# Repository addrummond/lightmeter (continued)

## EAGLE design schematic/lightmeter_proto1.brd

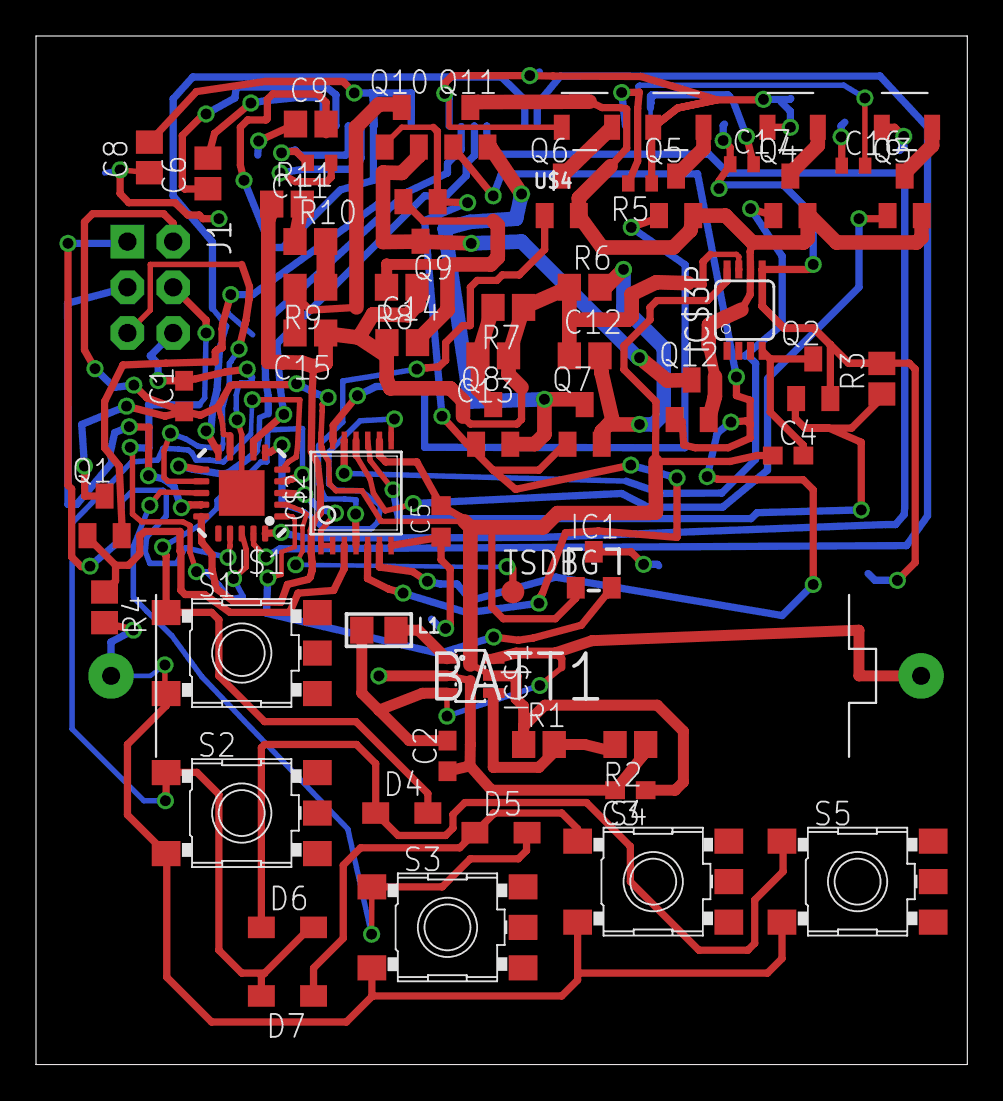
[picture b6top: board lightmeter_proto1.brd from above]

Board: 2 copper layers, 51.7 x 57.1 mm, 61 parts (0 on the bottom side), 54 nets.

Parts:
BATT1: AAA; 12BH412
C1, C4: µ1; C1608
C2, C3: 4µ7; C1608
C5: µ1; C0603K
C6, C8, C9: 1µ; C2012
C11: 1µ; C0402
C12, C13, C14, C15: 4µ7; C2012
C16: 4µ7; C0402
C17: 2µ2; C0402
D4, D5, D6, D7: SOD323-W
D8, D9, D10, D11: VEMD2523SLX01
IC1: TC1047SOT-23B; SOT-23B
IC$1: TI-TLV61220; SOT23-6L
IC$2: SN74HC164TSSOP-14; TSSOP14
IC$3P: AD8542RM; MSOP08
J1: AVR_SPI_PRG_6NS; 2X3-NS
L1: 4µ7; 0805
Q1, Q2, Q3, Q4, Q5, Q6, Q8, Q10, Q12: BSS123; SOT23
Q7, Q9, Q11: BSS84; SOT23
R1, R9, R10, R11: 1M; R2012
R2: 220k; R2012
R3, R4: 10k; R2012
R5: 390k; R0402
R6: 16k; R2012
R7: 130k; R2012
R8: 390k; R2012
S1, S2, S3, S4, S5: SKHMPSE010; SKHMPXE010
TSDBG: TPB1,27; B1,27
U$1: ATTINY1634MLF20; MLF20
U$4: UG-2864HSWEG01_0.96IN_WRAPAROUND

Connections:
AVRMISO: J1.1, U$1.17
AVRMOSI: J1.4, U$1.18
AVRRST: J1.5, U$1.12
AVRSCK: J1.3, U$1.14
DIODESW$1: IC$2.4, Q6.1
DIODESW$2: IC$2.13, Q5.1
DIODESW$3: IC$2.12, Q4.1
DIODESW$4: IC$2.11, Q3.1
GND: BATT1.-, C1.2, C2.1, C3.2, C5.1, C8.1, C9.1, C16.1, C17.1, D8.P$1, D9.P$1, D10.P$1, D11.P$1, IC1.3, IC$1.2, IC$2.7, IC$3P.5, J1.6, Q2.2, R2.1, R3.2, R4.2, R5.1, S1.3, S2.3, S3.3, S4.3, S5.3, U$1.8, U$1.GND, U$4.1, U$4.8, U$4.10, U$4.11, U$4.12, U$4.29, U$4.30
unnamed: IC$1.1, L1.2
unnamed: D8.P$2, Q6.3
unnamed: C14.2, Q9.2, R8.2
unnamed: C12.2, Q7.2, R6.2
unnamed: D9.P$2, Q5.3
unnamed: C4.2, IC$3P.4, Q2.3
unnamed: D5.C, D7.C, S4.1
unnamed: D4.C, D6.C, S5.1
unnamed: D10.P$2, Q4.3
unnamed: IC$1.4, R1.2, R2.2
unnamed: D11.P$2, Q3.3
unnamed: C16.2, U$4.27
unnamed: R9.1, R10.2
unnamed: C13.2, Q8.3, R7.2
unnamed: C6.2, U$4.2
unnamed: C6.1, U$4.3
unnamed: C8.2, C9.2, U$4.6, U$4.9
unnamed: R10.1, R11.2
unnamed: R5.2, U$4.26
unnamed: Q9.3, Q10.2, Q12.3
unnamed: C15.2, Q10.3, R9.2
unnamed: Q7.3, Q8.2, Q11.2
unnamed: TSDBG.TP, U$1.2
unnamed: C11.1, U$4.5
unnamed: C17.2, U$4.28
unnamed: IC$3P.6, Q3.2, Q4.2, Q5.2, Q6.2, Q11.3, Q12.2
unnamed: C11.2, U$4.4
unnamed: IC1.2, U$1.1
OAOUT: C12.1, C13.1, C14.1, C15.1, IC$3P.7, R6.1, R7.1, R8.1, R11.1, U$1.15
OAPWR: IC$2.10, Q2.1, R3.1
PBI$1: D4.A, S1.1, U$1.4
PBI$2: D6.A, D7.A, S2.1, U$1.5
PBI$3: D5.A, S3.1, U$1.13
SCRCLK: U$1.10, U$4.18
SCRCS: U$1.11, U$4.13
SCRDAT: U$1.19, U$4.19
SCRDC: U$1.20, U$4.15
SCRPWR: IC$2.3, Q1.1, R4.1
SCRRES: U$1.7, U$4.14
SRA: IC$2.1, IC$2.2, U$1.3
SRCLK: IC$2.8, U$1.6
STG$1: IC$2.5, Q7.1, Q8.1, Q9.1, Q10.1
STG$2: IC$2.6, Q11.1, Q12.1
VCC: BATT1.+, C2.2, IC$1.3, IC$1.6, L1.1
VREG: C1.1, C3.1, C4.1, C5.2, IC1.1, IC$1.5, IC$2.9, IC$2.14, IC$3P.8, J1.2, Q1.3, R1.1, U$1.9

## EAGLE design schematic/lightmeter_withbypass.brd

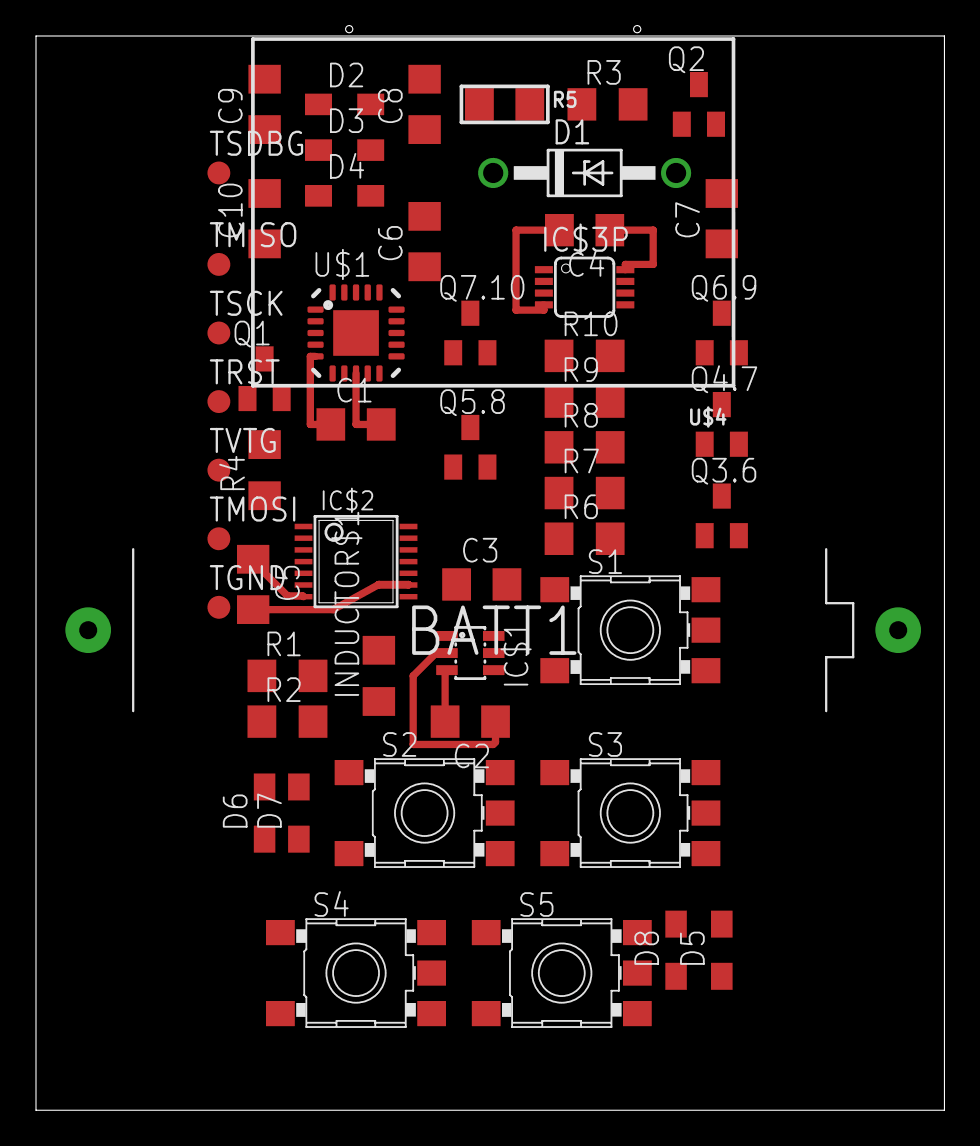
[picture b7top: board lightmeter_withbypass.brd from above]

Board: 2 copper layers, 50.5 x 59.7 mm, 54 parts (0 on the bottom side), 45 nets.

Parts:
BATT1: AAA; 12BH412
C1, C4, C5, C10: µ1; C1206
C2, C3, C6: 4µ7; C1206
C7: 2µ2; C1206
C8, C9: 2µ; C1206
D1: 1N4728; DO41Z10
D2, D3, D4, D5, D6, D7, D8: SOD323-W
IC$1: TI-TLV61220; SOT23-6L
IC$2: SN74HC164TSSOP-14; TSSOP14
IC$3P: AD8542RM; MSOP08
INDUCTOR$1: 4.7µH; R1206
Q1, Q2, Q3.6, Q4.7, Q5.8, Q6.9, Q7.10: BSS123; SOT23
R1, R9: 1M; R1206
R2: 220k; R1206
R3, R4: 10k; R1206
R5: 530k; 1206
R6: 1k; R1206
R7: 22k; R1206
R8: 330k; R1206
R10: 3.3M; R1206
S1, S2, S3, S4, S5: SKHMPSE010; SKHMPXE010
TGND: TPB1,27; B1,27
TMISO: TPB1,27; B1,27
TMOSI: TPB1,27; B1,27
TRST: TPB1,27; B1,27
TSCK: TPB1,27; B1,27
TSDBG: TPB1,27; B1,27
TVTG: TPB1,27; B1,27
U$1: ATTINY1634MLF20; MLF20
U$4: UG-2864HSWEG01_0.96IN_WRAPAROUND

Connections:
AVRMISO: TMISO.TP, U$1.17
AVRMOSI: TMOSI.TP, U$1.18
AVRRST: TRST.TP, U$1.12
AVRSCK: TSCK.TP, U$1.14
CPCLK1: C8.2, U$1.1
CPCLK2: C9.2, U$1.16
CPOUT: C10.1, D4.C, U$4.28
GND: BATT1.-, C1.2, C2.1, C3.2, C5.1, C7.2, C10.2, D1.A, IC$1.2, IC$2.7, IC$3P.5, Q1.2, Q2.2, R2.1, R3.2, R4.1, R5.2, S1.3, S2.3, S3.3, S4.3, S5.3, TGND.TP, U$1.8, U$1.GND
unnamed: IC$1.1, INDUCTOR$1.2
unnamed: C6.2, D1.C, IC$3P.6, Q3.6.3, Q4.7.3, Q5.8.3, Q6.9.3, Q7.10.3
unnamed: Q5.8.2, R8.2
unnamed: Q6.9.2, R9.2
unnamed: Q3.6.2, R6.2
unnamed: C4.2, IC$3P.4, Q2.3
unnamed: D6.C, D7.C, S4.1
unnamed: D5.C, D8.C, S5.1
unnamed: Q7.10.2, R10.2
unnamed: IC$1.4, R1.2, R2.2
unnamed: C8.1, D2.C, D3.A
unnamed: C9.1, D3.C, D4.A
unnamed: R5.1, U$4.26
unnamed: TSDBG.TP, U$1.2
unnamed: C7.1, U$4.27
OAOUT: C6.1, IC$3P.7, R6.1, R7.1, R8.1, R9.1, R10.1, U$1.15
OAPWR: IC$2.10, Q2.1, R3.1
PBI$1: D5.A, S1.1, U$1.4
PBI$2: D7.A, D8.A, S2.1, U$1.5
PBI$3: D6.A, S3.1, U$1.13
SCRCLK: U$1.10, U$4.18
SCRCS: U$1.11, U$4.13
SCRDAT: U$1.19, U$4.19
SCRDC: U$1.20, U$4.15
SCRGRND: Q1.3, U$4.1, U$4.8, U$4.10, U$4.11, U$4.12, U$4.29, U$4.30
SCRPWR: IC$2.3, Q1.1, R4.2
SCRRES: IC$2.4, U$1.7, U$4.14
SRA: IC$2.1, IC$2.2, U$1.3
SRCLK: IC$2.8, U$1.6
STG$1: IC$2.5, Q7.10.1
STG$2: IC$2.6, Q6.9.1
STG$3: IC$2.13, Q5.8.1
STG$4: IC$2.12, Q4.7.1
STG$5: IC$2.11, Q3.6.1
VCC: BATT1.+, C2.2, IC$1.3, IC$1.6, INDUCTOR$1.1
VREG: C1.1, C3.1, C4.1, C5.2, D2.A, IC$1.5, IC$2.9, IC$2.14, IC$3P.8, R1.1, TVTG.TP, U$1.9, U$4.6, U$4.9
X: Q4.7.2, R7.2

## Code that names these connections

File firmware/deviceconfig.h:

#ifndef DEVICE_CONFIG_H
#define DEVICE_CONFIG_H

#include <stdint.h>

#include <stm32f0xx_gpio.h>
#include <stm32f0xx_i2c.h>
#include <stm32f0xx_syscfg.h>

#define SYS_TICK_MAX 16777215

/*

STM32F030K6T6 configuration.

                  I  I  L
               B  2  2  R
               O  C  C  G     S  S
            V  O  S  S  E     T  T
            S  T  D  C  B     G  G
            S  0  A  L  L     1  2
            |  |  |  |  |  |  |  |
            ________________________
VDD      --|                       |-- SWDCLK/USBD+
           |                       |
         --|                       |-- SWDIO/USBD-
           |                       |
         --|                       |-- PBI$1
           |                       |
NRST     --|                       |-- PIEZOPOS
           |                       |
VDDA     --|                       |-- PIEZONEG
           |                       |
MEASURE1 --|                       |-- PBI$2
           |                       |
SCRPWR   --|                       |-- SCRRES
           |                       |
MEASURE2 --|                       |-- VDD
           |_______________________|
            |  |  |  |  |  |  |  |
            D  M  B  P  P  I     V
            I  I  A  I  I  N     S
            O  C  T  E  E  T     S
            D  O  V  Z  Z  E
            E  U  O  O  O  G
            S  T  L  P  N  C
            W     T  O  E  L
                  A  S  G  R
                  G
                  E
*/

//
// USB
//
#define USB_DPLUS_GPIO_PORT          GPIOA
#define USB_DPLUS_PIN                GPIO_Pin_14
#define USB_DMINUS_GPIO_PORT         GPIOA
#define USB_DMINUS_PIN               GPIO_Pin_13


//
// Pushbutton ports configuration.
//
#define PUSHBUTTON1_GPIO_PORT        GPIOA
#define PUSHBUTTON1_GPIO_PORT_SOURCE EXTI_PortSourceGPIOA
#define PUSHBUTTON1_PIN              GPIO_Pin_12
#define PUSHBUTTON1_PIN_SOURCE       GPIO_PinSource12
#define PUSHBUTTON1_EXTI             EXTI12
#define PUSHBUTTON1_EXTI_LINE        EXTI_Line12

#define PUSHBUTTON2_GPIO_PORT        GPIOA
#define PUSHBUTTON2_GPIO_PORT_SOURCE EXTI_PortSourceGPIOA
#define PUSHBUTTON2_PIN              GPIO_Pin_9
#define PUSHBUTTON2_PIN_SOURCE       GPIO_PinSource9
#define PUSHBUTTON2_EXTI             EXTI9
#define PUSHBUTTON2_EXTI_LINE        EXTI_Line9


//
// Resistor/diode switches configuration.
//
#define DIODESW_PORT        GPIOA
#define DIODESW_PIN         GPIO_Pin_3


//
// ADC pins for light sensor measurement.
//

#define MEASURE1_GPIO_PORT   GPIOA
#define MEASURE1_PIN         GPIO_Pin_0
#define MEASURE1_ADC_CHANNEL ADC_Channel_0
#define MEASURE2_GPIO_PORT   GPIOA
#define MEASURE2_PIN         GPIO_Pin_2
#define MEASURE2_ADC_CHANNEL ADC_Channel_2
#define DIODESW_GPIO_PORT    GPIOA
#define DIODESW_PIN          GPIO_Pin_3
#define INTEGCLR_GPIO_PORT   GPIOA
#define INTEGCLR_PIN         GPIO_Pin_5


//
// I2C
//

#define I2C_I2C              I2C1
#define I2C_CLK              RCC_APB1Periph_I2C1
#define I2C_SDA_GPIO_PORT    GPIOB
#define I2C_SDA_PIN          GPIO_Pin_7
#define I2C_SDA_SOURCE       GPIO_PinSource7
#define I2C_SCL_GPIO_PORT    GPIOB
#define I2C_SCL_PIN          GPIO_Pin_6
#define I2C_SCL_SOURCE       GPIO_PinSource6
#define I2C_SDA_GPIO_CLK     RCC_AHBPeriph_GPIOB
#define I2C_SCL_GPIO_CLK     RCC_AHBPeriph_GPIOB


//
// Screen
//

#define DISPLAY_RESET_GPIO_PORT  GPIOA
#define DISPLAY_RESET_PIN        GPIO_Pin_8
#define DISPLAY_POWER_GPIO_PORT  GPIOB
#define DISPLAY_POWER_PIN        GPIO_Pin_4

#endif

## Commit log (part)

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2015-05-26 Figure out component values for oscillator and some other tweaks.
2015-05-26 Move somewhat precariously placed via.
2015-05-26 Some tweaks to silkscreen.
2015-05-26 Improve connectivity of ground polygon.
2015-05-26 Make dimensions of battery connector more realistic.
2015-05-26 Minor.
2015-05-27 Improve ground polygon connectivity.
2015-05-27 Remove GND jumper on bottonm layer
2015-05-27 More work on improving coverage of ground polygon.
2015-05-27 Fix some DRC errors.
2015-05-27 Update jumper count.
2015-05-27 Some modifications to battery plug socket and some attempts to make room for better piezo connectors.
2015-05-27 DRC check passes again.
2015-05-27 New piezo connector layout complete.
2015-05-27 Add missing trace to board.
2015-05-27 Fix silly mistake (one of the piezo wire holes was below the screen).
2015-05-27 Update bom.partslist with links to some useful Mouser product pages.
2015-05-27 Remove parts.numbers (replaced by bom.partslist)
2015-05-27 Minor correction to schematic description and layout improvement.
2015-05-27 Consolidate 3300pF caps
2015-05-27 Change to silkscreen.
2015-05-27 Update to silkscreen.
2015-06-02 Add second Seeed prototype board to ordered/
2015-06-11 Some improvements to buildsheet.py
2015-06-11 Update code for pin config of new Seeed prototype.
2015-06-11 More code updates.
2015-06-11 Fix MOSFET logic in display.c
2015-06-11 Some updates to partfinder.py
2015-06-11 Some tweaks to layout.
2015-06-12 Update bom.partslist with ezmate crimp terminals.
2015-06-12 Minor updates to schematic.
2015-06-12 Get rid of LREGENABLE (STM32 needs AVDD to be high to start up)
2015-06-12 Get rid of LREGENABLE
2015-06-12 Some fixes to meter.c
2015-06-12 Some more work on meter.c
2015-06-12 Take display_init out of sysinit_init
2015-06-12 More improvements to meter.c
2015-06-12 More work on metering etc.
2015-06-12 Fix to display.c
2015-06-13 Some progress on metering mess.
2015-06-13 Various significant improvements to metering.
2015-06-14 Is it finally fixed (??)
2015-06-14 Some tweaks to 'stabilize' function in meter.c
2015-06-14 TEMP
2015-06-14 Fix up meter mess following correction to board.
2015-06-14 Fix REFLECTIVE/INCIDENT swap.
2015-06-14 Some more work on exposure stuff.
2015-06-14 Tweaks to meter.c
2015-06-15 Some work on ND filters etc.
2015-06-15 Some more work on metering/calibration stuff.
2015-06-15 Significant improvement to speed of integrading meter reading code.
2015-06-16 Fix logic error in meter_take_raw_integrated_readings
2015-06-16 Improvements to show_calibration_info
2015-06-16 Some work on mains noise filtering etc.
2015-06-17 Some improvements to ground plane connectivity.
2015-06-18 Some more (incomplete) work on ground plane connectivity.
2015-06-21 Replace generic inductor with specific model in bom.partslist
2015-06-21 More work on improving PCB layout.
2015-06-21 More work on board and schematic.
2015-06-22 More work on board layout.
2015-06-22 Some work on pcb clearences.
2015-06-22 More work on board etc.
2015-06-22 More work on board/schematic.
2015-06-22 Use correct battery charger IC for LiPo battery (!) (same pin layout)
2015-06-23 More work on schematic and board; selectable charging rates.
2015-06-24 Minor updates to board layout.
2015-06-24 Some work on silkscreen.
2015-06-24 Add EEPROM
2015-07-02 Some initial work on redefining ev_with_fracs_t as uint_fast16_t
2015-07-02 Firmware now compiles with new ev_with_fracs_t implementation.
2015-07-04 Some updates to board and schematic.
2015-07-04 Some improvements to ground polygon.
2015-07-04 Some fixes to tests in exposure.c
2015-07-04 Some work on mic stuff.
2015-07-04 Set higher optimization setting for 'goetzel' function.
2015-07-04 Some possible further progress on freq stuff?
2015-07-04 Frequency detection now working much better after fixing some sign bugs in goetzel implementation and in piezo.c
2015-07-04 More work on goetzel stuff.
2015-07-04 Normalizing for power thingy doesn't seem to do anything useful.
2015-07-04 More work on goetzel.c
2015-07-04 Add bypass cap for mic
2015-07-05 TEMP WORK ON USB SERIES.
2015-07-05 Add debugging_write_int32
2015-07-05 Frequency detection via goetzel is now more-or-less working.
2015-07-06 Some minor optimizations to goetzel
2015-07-06 More goetzel fiddling.
2015-07-06 Some webconfig.js tweaking.
2015-07-06 Some possible initial partial success in ultrasound master->slave data transmission
2015-07-06 Fix some nasty bugs in 'encode_signal' in webconfig.js
2015-07-06 Some other tweaks to webconfig.js
2015-07-06 Remove some debug code in webconfig.js
2015-07-06 Some more (so far unsuccessful) work on decoding.
2015-07-06 Fix logic bug in piezo_read_data (still doesn't work)
2015-07-06 Some more work on piezo.c
2015-07-07 Factor out some code into hfsdp module.
2015-07-07 Some useful test code added to hfsdp.c
2015-07-08 Various fiddling.
2015-07-08 Some improvements/fixes to goetzel.c test code.
2015-07-09 Offline encoding/decoding for HFSDP appears to be working.
2015-07-09 Fix typo in comment in hfsdp.c
2015-07-09 Some semi-promising initial results using mic.
2015-07-11 Improvements to calccoeffs.py
2015-07-11 Remove silly mistake regarding coefficient calculation
2015-07-11 Back to square one but with correct timer-determined sample rate.
2015-07-11 Add some notes on dma timer in piezo.c
2015-07-11 Some important fixes to mic stuff.
2015-07-11 JFC.
2015-07-13 Some work on goetzel mess.
2015-07-13 Add offset option for goetzel
2015-07-13 Back at square one -- wobbly goetzel.
2015-07-13 Huge progress on hfsdp
2015-07-13 Good chance that HFSDP reception will work now. SysClk is 8MHz not 48MHz
2015-07-13 NO WORKY
2015-07-13 WORK
2015-07-13 More improvements to hfsdp stuff, appears to be more-or-less working.
2015-07-14 Some initial work on hamming.c and hamming.h
2015-07-14 Some more work on hamming; still a bit buggy.
2015-07-14 Hamming code now working.
2015-07-14 Some work on generating JS code from hamming.c
2015-07-14 Add hamming module to build.sh
2015-07-14 Remove unused variable from hamming.c
2015-07-14 Javascript version of hamming code appears to work.
2015-07-14 Stop parseInt from being called during computation in hamming.c (hamming.js)
2015-07-14 Add hamming.js to vc, since hamming.c is not likely to change all that often.
2015-07-15 More work on hamming stuff.
2015-07-15 Hamming encoding and decoding algorithm now working.
    Back at square one re problem with noisy signal generation in webconfig.js
2015-07-15 Get piezo_read_data to output in compacted form.
2015-07-16 Remove unused code from webconfig.js
2015-07-16 Some more work on webconfig.js
2015-07-16 Offset clock signal
2015-07-16 Fix bug in piezo.c
2015-07-16 Some more work on mic stuff.
2015-07-16 Some more work on hamming stuff.
    hamming_bitshift_buffer_forward now appears to be working correctly
    hamming_scan_for_init_sequence still untested
2015-07-17 Some more work on hamming stuff. hamming.c is mostly complete and working now.
2015-07-18 Some more work on hamming stuff.
2015-07-18 Add some debugging code back in to piezo.c
2015-07-18 Remove misguided clock signal offset.
2015-07-18 Some improvements to hamming API
2015-07-18 Sending on short messages working (but very very unreliably)
2015-07-20 Some initial work on moving to CPFSK in webconfig.js
2015-07-20 Some further progress on CMFSK encoding in webconfig.js
2015-07-20 Code cull in webconfig.js
2015-07-20 Minor improvement to webconfig.js
2015-07-23 Some very early work on moving to CPFSK
2015-07-23 More HFSDP stuff.
2015-07-23 More work on HFSDP stuff.
2015-07-23 Some progress on HFSDP
2015-07-23 Text transmission via HFSDP occasionally working.
2015-07-23 Minor update to hamming.c hamming.js
2015-08-31 Remove unnecessary and possible unhelpful cap in mic preamp circuit
2015-08-31 Initial work on switching to bluetooth LE from ultrasound
2015-08-31 Some initial work on bluetooth
2015-09-01 more work on board/schematic
2015-09-01 Some more work on board/schematic for bluetooth
2015-09-01 More work on bluetooth stuff.
2015-09-01 Some significant progress on bluetooth layout.
2015-09-01 Add USB protector ic
2015-09-02 More work on bluetooth and usb protection diode ic
2015-09-02 More work on layout.
2015-10-08 Changes to board layout.
2015-10-08 Some work on board layout
2015-10-10 More work on pcb layout.
2015-10-12 Improve ground plane connectivity
2015-10-13 Major progress on first draft of board layout -- design rule checks now complete
2015-10-13 Some corrections to board and schematic.
2015-10-13 Remove leftover piezo schematic
2015-10-14 blah
2015-10-25 Remove unneded cap and more work on board layout.
2015-11-08 Some progress on board layout.
2015-11-08 More improvements to layout.
2015-11-08 Sort out layout problem with one of the caps associated with bluetooth chip
2015-12-22 Shift screen and buttons up.
2015-12-22 Some work on making room for bottom layer signals running along bottom of board
2015-12-22 Some work on making room for bluetooth antenna.
2015-12-23 Add 2450BM14A0002 (balun) to lightmeter.lbr
2015-12-23 Some further work on bluetooth etc.
2015-12-23 Add 2450AT18A100 (bluetooth antenna) to lightmeter.lbr
2015-12-23 Some initial work on placing balun and antenna for bluetooth
2015-12-23 Some work on making room for antenna.
2015-12-24 More work on positioning arial.
2015-12-24 More work on positioning antenna.
2015-12-24 Shift things areound problematic screw hole in bottom left.
2015-12-24 fiddling
2015-12-24 More work on bluetooth-related layout issues.
2015-12-24 DRC fix.
2015-12-24 Add missing GND connection.
2015-12-24 Some tidying up.
2015-12-25 Remove unused solder jumper.
2015-12-25 More work on fixing DRC errors.
2015-12-25 DRC errors all fixed now.
2015-12-25 Some improvements to ground plane connnectivity.
2015-12-26 Some more work on ground plane connectivity.
2015-12-27 Various tweaks to silkscreen and layout.
2016-01-16 Some code style changes to exposure.c
2016-01-16 Add some asserts for undefined states in exposure.c
2016-02-06 Update schematic with usb protection diode ic
2016-02-06 Find suitable 16MHz crystal.
2016-02-06 More tweaks to board -- looks about done.
2016-02-06 All air wires now routed.
2016-02-06 Restrict ground polygon under crystals
2016-02-12 Some improvements to board layout.
2016-02-12 Add battery charger / power mux IC to lightmeter.lbr
2016-02-12 More work on new mux design
2016-02-13 More work on bat charger ic
2016-02-13 More work on new layout.
2016-02-13 Tidy some traces.
2016-02-13 Add pushbutton package for http://www.mouser.co.uk/ProductDetail/E-Switch/TL3342F260QG/?qs=sGAEpiMZZMsgGjVA3toVBFs%252bYYgf97FdJqg0XgoOhVc%3d
2016-02-14 Dont bother with charger temp control, just use a single regular resistor.
2016-02-22 Add Readme.markdown
2016-02-22 Add resistor for charger temp control.
2016-02-22 Switch to Make-based build system
2016-02-22 Remove some files relating to old build system.
2016-02-22 Add comment to Makefile with link to info on build method.
2016-02-25 = -> := in Makefile
2016-02-25 Some fixes to build process; test code can now be built via Makefile
2016-02-26 Add support for outputting shutter speeds at quarter and half stop precision in exposure.c
2016-03-03 Use more abstract interface to ev_with_fracs_t in fps_and_angle_to_shutter_speed
2016-03-07 Remove separate LDO voltage regulator for AVREG -- probably unnecessary and gave rise to too much idle power consumption.
2016-03-07 More work on fixing DRC violations.
2016-03-07 Tidy up silkscreen a bit.
2016-03-07 Add another VCC polygon.
2016-03-09 Some minor fixes to shutter speed tables.
2016-03-10 Minor layout change.
2016-03-11 Fix some bugs in buildsheet.py
2016-03-11 Use light grey vs. black instead of black vs red in buildsheet.py
2016-03-11 Add missing include in i2c.h (did not give rise to an error because it was included elsewhere, but should be here)
2017-05-02 Remove some outdated code/docs that was still hanging around.
2017-05-02 Some initial work on exposure compensation.
2017-05-02 Minor changes to test code in main.c and accel.c.
